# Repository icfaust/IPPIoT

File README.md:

# IPPIoT
ESP8266 native Non-OS SDK 7-segment JSON number display

This is the necessary documentation for someone to collect the necessary components and compile the right code for
their very own web JSON reader.  Its pretty basic with a hardcoded wifi and website to access for the JSON. 

The components should all work well together, using the CATIA files, EAGLE files, and list of components to create
the device.  If you end up trying to build one, let me know!!!!!

The code does require a successfully installed pfaclon esp-open-sdk installation.  The makefile should work pretty straight-forwardly on a Ubuntu or Linux distro (thats what I used).

You can go over to my personal website for a more in-depth explanation of the design process with photos.

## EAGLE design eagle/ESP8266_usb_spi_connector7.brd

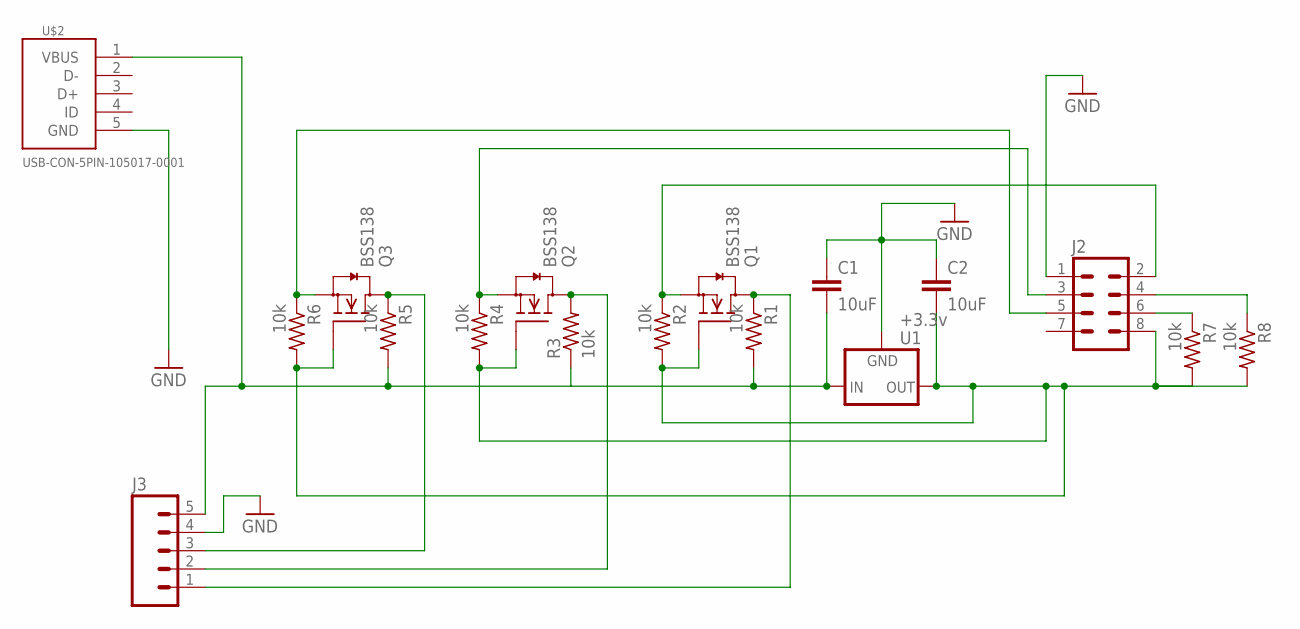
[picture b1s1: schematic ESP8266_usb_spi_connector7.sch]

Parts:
C1, C2: 10uF; 1206
J2: M04X2; 2X4
J3: M05PTH; 1X05
Q1, Q2, Q3: BSS138; SOT23
R1, R2, R3, R4, R5, R6, R7, R8: 10k; M1206
U1: +3.3v; TO-252
U$2: USB-CON-5PIN-105017-0001; USB-MICRO-MOLEX-105017-0001

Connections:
GND: C1.1, C2.1, J2.1, J3.4, U1.3 (GND), U$2.5 (GND)
unnamed: J3.3, Q3.3 (D), R5.1
unnamed: J2.3, Q2.2 (S), R4.1
unnamed: C2.2, J2.8, Q1.1 (G), Q2.1 (G), Q3.1 (G), R2.2, R4.2, R6.2, R7.2, R8.2, U1.2 (OUT)
unnamed: J3.2, Q2.3 (D), R3.2
unnamed: J3.1, Q1.3 (D), R1.1
unnamed: J2.5, Q3.2 (S), R6.1
unnamed: J2.2, Q1.2 (S), R2.1
unnamed: C1.2, J3.5, R1.2, R3.1, R5.2, U1.1 (IN), U$2.1 (VBUS)
unnamed: J2.6, R7.1
unnamed: J2.4, R8.1

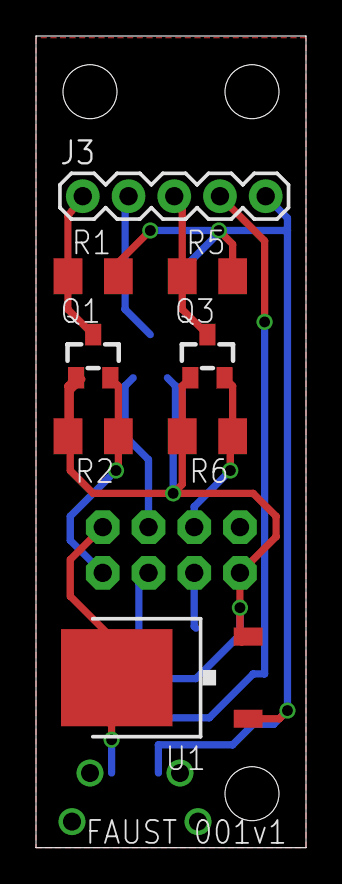
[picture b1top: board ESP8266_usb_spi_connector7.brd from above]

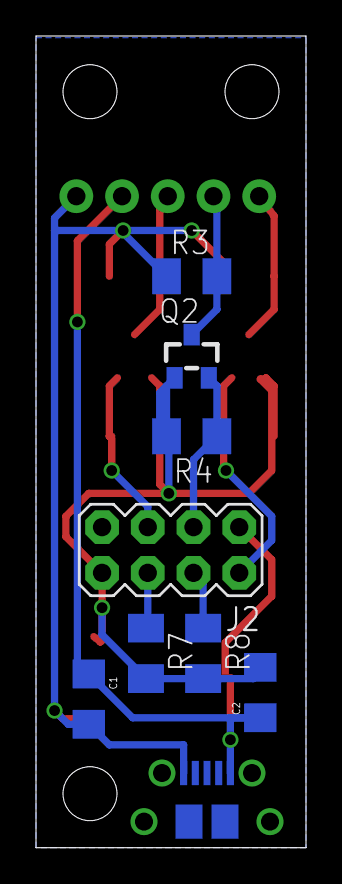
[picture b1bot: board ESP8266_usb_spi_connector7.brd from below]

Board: 2 copper layers, 15.0 x 45.1 mm, 17 parts (9 on the bottom side), 11 nets.

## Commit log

2018-05-18 Should have done this sooner
    Contains all of the files I needed for my ESP8266 interface
2018-06-17 updates to structure
2018-06-17 added CATIA files for structure
2018-06-17 removed redundant files
2018-06-25 better board spec
2018-06-25 updated eagle documents
2018-06-25 further cleaning
2018-06-25 updated files to actual production versions
2018-06-25 added necessary parts list
2018-06-29 mistake on number of 10k resistors

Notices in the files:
parts and their libraries:
SparkFun-Passives: Licensing: Creative Commons ShareAlike 4.0 International - https://creativecommons.org/licenses/by-sa/4.0
m-pad-2.1: License : GNU General Public License version 2 (see bottom)
